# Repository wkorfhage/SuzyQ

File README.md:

# SusyQ
SusyQ adapter for a Chromebook using the connection definition on
 [the hdctools website](https://chromium.googlesource.com/chromiumos/third_party/hdctools/+/HEAD/docs/ccd.md#SuzyQ-SuzyQable).

 This uses the following parts

 |Description|Part Number|LCSC Part Number|Quantity|
 |16P USB-C socket|USB-C_SMD-TYPE-C-31-M-12|C165948|2|
 |22K 0805 SMD resistor|||1|
 |45.3K 0805 SMD resistor|||1|

 This ignores the impedance standards for the USB data lines and is just a standard 2-layer board.

 The board is 11 mm in diameter, so you can insulate it with clear heat-shrink tubing 15-20 mm in diameter

 This project uses KiCad 8

## Versions

### 1.0

This version uses 2 USB-C female connectors.

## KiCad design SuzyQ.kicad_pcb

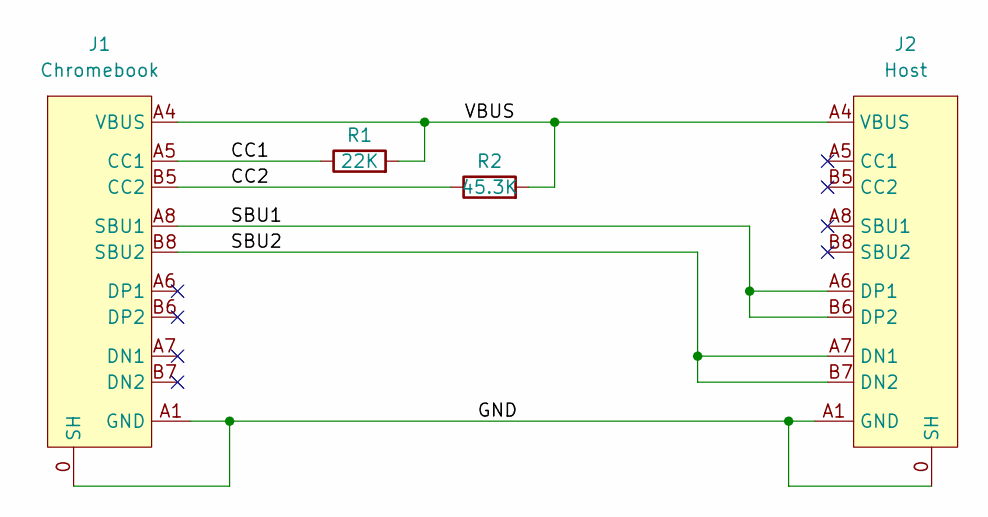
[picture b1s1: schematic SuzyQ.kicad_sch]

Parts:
J1: Chromebook; USB-C_SMD-TYPE-C-31-M-12; LCSC Part C165948
J2: Host; USB-C_SMD-TYPE-C-31-M-12; LCSC Part C165948
R1: 22K; R_0805_2012Metric_Pad1.20x1.40mm_HandSolder
R2: 45.3K; R_0805_2012Metric_Pad1.20x1.40mm_HandSolder

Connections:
/CC1: J1.A5 (CC1), R1.1
/CC2: J1.B5 (CC2), R2.1
/GND: J1.0 (SH), J1.1 (SH), J1.2 (SH), J1.3 (SH), J1.A1 (GND), J1.A12 (GND), J1.B1 (GND), J1.B12 (GND), J2.0 (SH), J2.1 (SH), J2.2 (SH), J2.3 (SH), J2.A1 (GND), J2.A12 (GND), J2.B1 (GND), J2.B12 (GND)
/SBU1: J1.A8 (SBU1), J2.A6 (DP1), J2.B6 (DP2)
/SBU2: J1.B8 (SBU2), J2.A7 (DN1), J2.B7 (DN2)
/VBUS: J1.A4 (VBUS), J1.A9 (VBUS), J1.B4 (VBUS), J1.B9 (VBUS), J2.A4 (VBUS), J2.A9 (VBUS), J2.B4 (VBUS), J2.B9 (VBUS), R1.2, R2.2

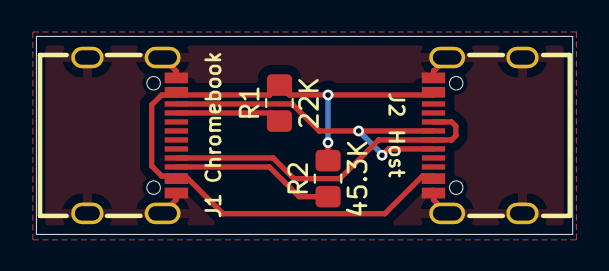
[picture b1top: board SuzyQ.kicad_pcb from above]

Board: 2 copper layers, 29.8 x 11.0 mm, 4 parts (0 on the bottom side), 6 nets.

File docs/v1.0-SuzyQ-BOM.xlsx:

Reference | Value | Description | Footprint | LCSC Part
J1 | Chromebook | 16P 5A Female Type-C SMD USB Connector | LCSC:USB-C_SMD-TYPE-C-31-M-12 | C165948
J2 | Host | 16P 5A Female Type-C SMD USB Connector | LCSC:USB-C_SMD-TYPE-C-31-M-12 | C165948
R1 | 22K | Resistor | Resistor_SMD:R_0805_2012Metric_Pad1.20x1.40mm_HandSolder
R2 | 45.3K | Resistor | Resistor_SMD:R_0805_2012Metric_Pad1.20x1.40mm_HandSolder

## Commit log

2024-12-02 version 1.0 files
2024-12-02 Forgot to save schematic
